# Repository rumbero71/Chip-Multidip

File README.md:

CHIP MultiDIP

This is a purpose-made DIP for NextthingCO's C.H.I.P. 
Functions:
-USB-Serial
-SD Card reader
-I2C OLED Display
-4 GPIO buttons
-3 GPIO LEDs
-Power button
-FEL Mode button

I created a case for C.H.I.P. and this DIP:
http://www.thingiverse.com/thing:2154924

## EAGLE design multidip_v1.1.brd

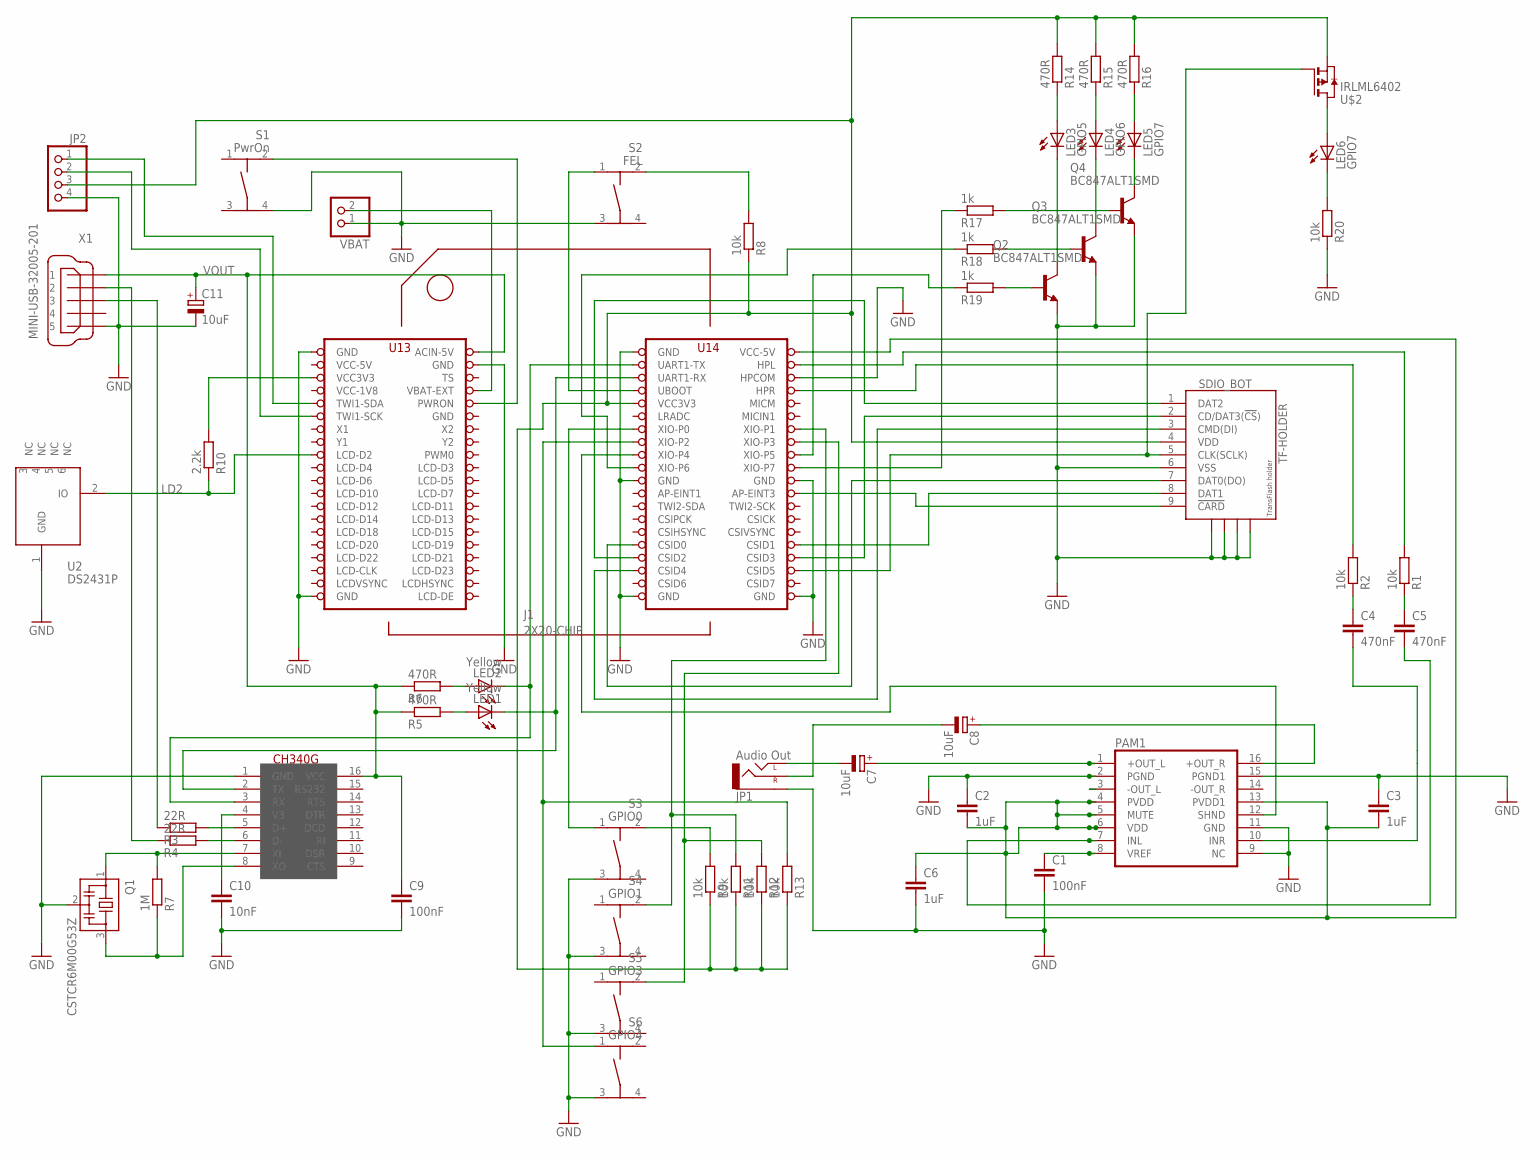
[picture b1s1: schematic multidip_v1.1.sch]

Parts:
C1, C9: 100nF; C0805
C2, C3, C6: 1uF; C0805
C4, C5: 470nF; C0805
C7, C8, C11: 10uF; CT3216
C10: 10nF; C0805
J1: 2X20-CHIP; 2X20CHIP_OFFSET-TH
JP1: Audio Out; AUDIO-JACK
JP2: PINHD-1X4; 1X04
LED1, LED2: Yellow; CHIP-LED0805
LED3: GPIO5; CHIP-LED0805
LED4: GPIO6; CHIP-LED0805
LED5, LED6: GPIO7; CHIP-LED0805
PAM1: PAM8403; SOP-16
Q1: CSTCR6M00G53Z; CSTCR6M
Q2, Q3, Q4: BC847ALT1SMD; SOT23
R1, R2, R8, R9, R11, R12, R13, R20: 10k; MINI_MELF-0204W
R3, R4: 22R; MINI_MELF-0204W
R5, R6, R14, R15, R16: 470R; MINI_MELF-0204W
R7: 1M; MINI_MELF-0204W
R10: 2.2k; MINI_MELF-0204W
R17, R18, R19: 1k; MINI_MELF-0204W
S1: PwrOn; TASTER-9314_SMD
S2: FEL; TASTER-9314_SMD
S3: GPIO0; TASTER-9314_SMD
S4: GPIO1; TASTER-9314_SMD
S5: GPIO3; TASTER-9314_SMD
S6: GPIO4; TASTER-9314_SMD
SDIO_BOT: TF-HOLDER; TF-PULL
U2: DS2431P; TSOC6
U$1: CH340G; SOIC16
U$2: IRLML6402; SOT-23
VBAT: PINHD-1X2; 1X02
X1: MINI-USB-32005-201; 32005-201

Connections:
GND: C1.2, C2.1, C3.1, C6.2, C9.2, C10.2, C11.-, J1.GND@1 (GND), J1.GND@2 (GND), J1.GND@3 (GND), J1.GND@4 (GND), J1.GND@5 (GND), J1.GND@6 (GND), J1.GND@7 (GND), J1.GND@8 (GND), J1.GND@10 (GND), J1.HPCOM, JP1.SLEEVE, JP2.4, PAM1.2 (PGND), PAM1.9 (NC), PAM1.11 (GND), PAM1.15 (PGND1), Q1.2, Q2.2 (E), Q3.2 (E), Q4.2 (E), R20.1, S1.4, S2.3, S3.3, S4.3, S5.3, S6.3, SDIO_BOT.6 (VSS), SDIO_BOT.S1, SDIO_BOT.S2, SDIO_BOT.S3, SDIO_BOT.S4, U2.1 (GND), U$1.1 (GND), VBAT.1, X1.5
LD2: J1.LCD-D2, R10.1, U2.2 (IO)
unnamed: J1.VCC3V3, R10.2
unnamed: J1.CSID3, SDIO_BOT.2 (CD/DAT3(!CS!))
unnamed: J1.CSID0, SDIO_BOT.7 (DAT0(DO))
unnamed: J1.CSID4, SDIO_BOT.3 (CMD(DI))
unnamed: J1.CSID5, SDIO_BOT.5 (CLK(SCLK)), U$2.1 (G)
unnamed: J1.CSID1, SDIO_BOT.8 (DAT1)
unnamed: C2.2, C3.2, C6.1, J1.VCC5V@1 (VCC-5V), PAM1.4 (PVDD), PAM1.5 (MUTE), PAM1.6 (VDD), PAM1.13 (PVDD1)
unnamed: LED3.C, Q2.3 (C)
unnamed: J1.CSID2, SDIO_BOT.1 (DAT2)
unnamed: LED4.C, Q3.3 (C)
unnamed: C7.+, PAM1.1 (+OUT_L)
unnamed: C7.-, JP1.TIP (LEFT)
unnamed: C8.+, PAM1.16 (+OUT_R)
unnamed: C8.-, JP1.RING (RIGHT)
unnamed: R3.1, X1.3
unnamed: J1.AP-EINT3, SDIO_BOT.9 (!CARD)
unnamed: Q4.1 (B), R17.2
unnamed: J1.HPL, R1.2
unnamed: C1.1, PAM1.8 (VREF)
unnamed: C4.1, R2.1
unnamed: C5.1, R1.1
unnamed: J1.XIO-P1, R11.2, S4.2
unnamed: J1.XIO-P3, R12.2, S5.2
unnamed: J1.XIO-P0, S3.1
unnamed: J1.XIO-P2, R13.2, S6.1
unnamed: J1.XIO-P4, PAM1.12 (SHND)
unnamed: J1.BAT (VBAT-EXT), VBAT.2
unnamed: J1.PWRON, S1.2
unnamed: J1.HPR, R2.2
unnamed: C4.2, PAM1.10 (INR)
unnamed: C5.2, PAM1.7 (INL)
unnamed: R3.2, U$1.5 (D+)
unnamed: R4.2, U$1.6 (D-)
unnamed: Q1.1, R7.2, U$1.7 (XI)
unnamed: Q1.3, R7.1, U$1.8 (XO)
unnamed: C10.1, U$1.4 (V3)
unnamed: J1.UART1-TX, LED2.C, U$1.3 (RX)
unnamed: J1.UART1-RX, LED1.C, U$1.2 (TX)
unnamed: LED2.A, R6.2
unnamed: LED1.A, R5.2
unnamed: J1.FEL (UBOOT), S2.1
unnamed: R8.2, S2.2
unnamed: LED5.C, Q4.3 (C)
unnamed: R9.2, S3.2
unnamed: J1.VCC3V3@1 (VCC3V3), JP2.3, R8.1, R9.1, R11.1, R12.1, R13.1, R14.2, R15.2, R16.2, SDIO_BOT.4 (VDD), U$2.2 (S)
unnamed: LED3.A, R14.1
unnamed: LED4.A, R15.1
unnamed: LED5.A, R16.1
unnamed: J1.XIO-P5, R19.1
unnamed: J1.XIO-P6, R18.1
unnamed: J1.XIO-P7, R17.1
unnamed: R4.1, X1.2
unnamed: J1.TWI1-SCK, JP2.2
unnamed: J1.TWI1-SDA, JP2.1
unnamed: Q3.1 (B), R18.2
unnamed: Q2.1 (B), R19.2
unnamed: LED6.A, U$2.3 (D)
unnamed: LED6.C, R20.2
VCC-1V8: J1.VCC1V8 (VCC-1V8)
VCC-5V: J1.VCC5V@0 (VCC-5V)
VOUT: C9.1, C11.+, J1.CHG-IN (ACIN-5V), R5.1, R6.1, U$1.16 (VCC), X1.1

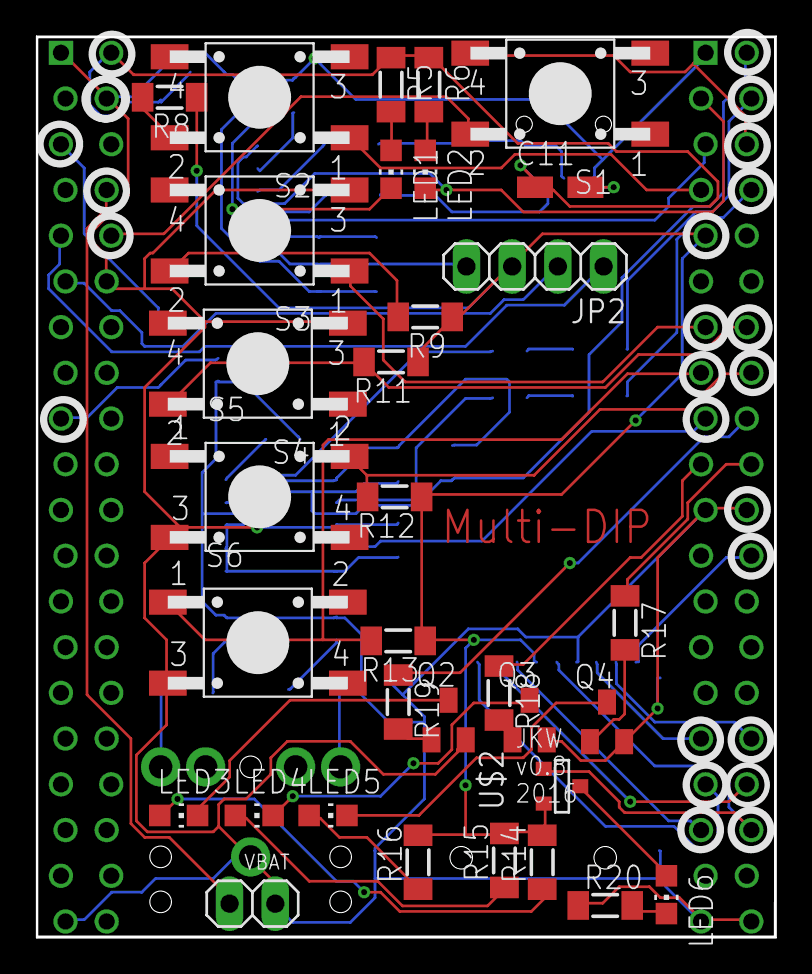
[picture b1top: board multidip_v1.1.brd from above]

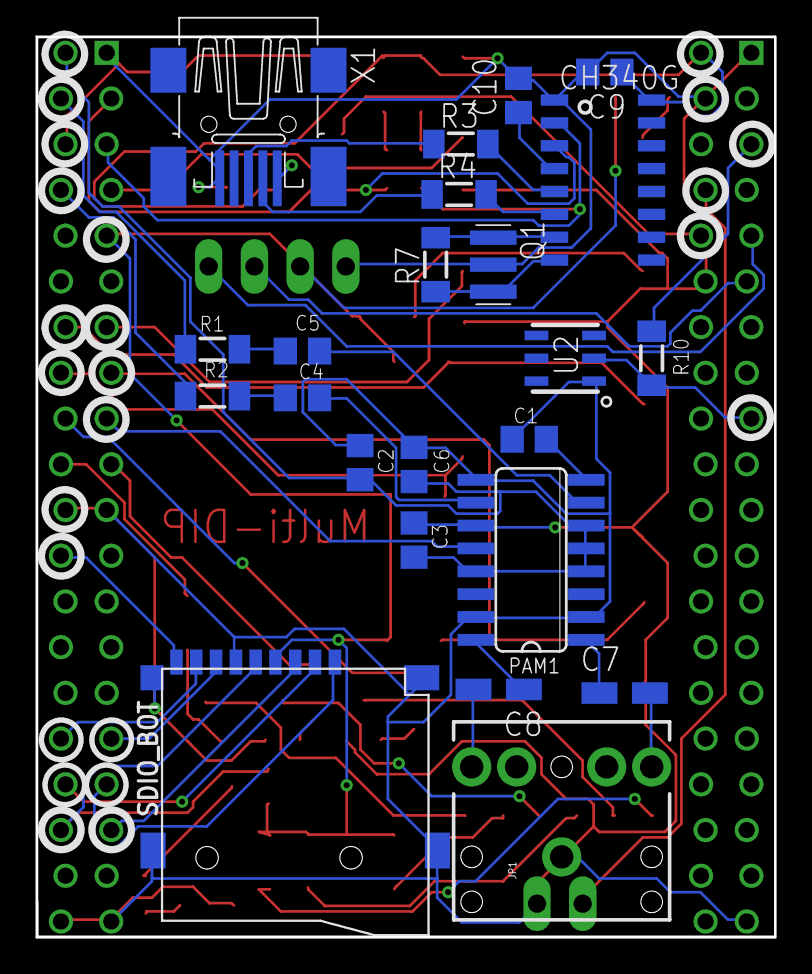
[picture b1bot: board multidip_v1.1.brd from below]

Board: 2 copper layers, 41.0 x 50.0 mm, 57 parts (23 on the bottom side), 61 nets.

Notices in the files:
parts and their libraries:
SparkFun-Connectors: Licensing: Creative Commons ShareAlike 4.0 International - https://creativecommons.org/licenses/by-sa/4.0
